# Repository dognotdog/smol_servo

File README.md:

# Project Layout

## firmware48

Contains files specific to 48pin STM32G431 on the stm32-nema17-servo board.

## mechaduino-firmware

Firmware for Mechaduino's SAMD21G18A Cortex M0+.

## hardware

Hardware design files for Schematic and PCB.

## tests

There is a basic harness in place to use [Unity](https://github.com/ThrowTheSwitch/Unity) for unit testing. Create `foo_test.c` modules for testing, and `foo_test.mk` makefiles for additional setup.

# Calculations

### Current Sense Shunt Resistor Value

Rated continous current 8A, max. Bus Voltage 50V, min. load 1R

 - 1206 can dissipate 1.5W usually, using a conservative 1W for the rated current: P/I^2 -> Rs < 15.6mOhm

With a 1R load on a 50V bus, up to 50A could flow at once, but hopefully motor inductance smoothes that out. Assuming 50kHz, 2mH winding inductance:
	V = L * di/dt -> di/dt = V/L = 25kA/s @ 50kHz = 0.5 A/cycle

### Gate Drive

The required charge pump current is
	I_VCP = 3 * Q_G * f_PWM.

DRV8323 charge pump VBUS limits:
6V -> 10mA
8V -> 15mA
10V -> 20mA
13V -> 25mA

#### NTTFS4937N

Q_G = 35.5 nC

I_VCP = 3.55 mA @ 100kHz
I_VCP = 1.78 mA @ 50kHz

Charge pump current capacity is well over required charge pump current.

#### FDMC86570L

Q_G < 88 nC

I_VCP = 8.8 mA @ 100kHz
I_VCP = 4.4 mA @ 50kHz

#### FDMC86183

Q_G ~ 15 nC
Q_gd ~ 3.4 nC

### Passive NSS OR circuit

3.3V, 5pF gate capacitance, 8mA sink/source per pin -> 412.5 Ohm minimum resistance

f_RC = 1 / 2pi R C

for R=470 that is 67.7MHz
for R=1k that is 31.8MHz
for R=2.2k that is 14.4MHz

max SPI frequency is 10MHz. 1k for both lines seems sufficiently fast and will not exceed max current on pin. Only one will be actively pulled high, the other will be in high impedance mode, but 1k is safe even if both are actively driven against the NSS pin.

# Electrical Motor Driving

## RL Circuit
The principal equation for an RL circuit, as is assumed for a motor winding, describing the relationship between voltage and current is:
`V = L * di/dt + R i`
or in differential form
```
	        V - R i
	di/dt = -------
	           L
```

### Discrete Time RL Equation

In discrete time, with n=0,1,2... indices going backward in time, the equation becomes
`V_0 = L * (i_0 - i_1) / T + R i_0`
solving for L
```
      V_0 - R i_0
L = T -----------
       i_0 - i_1
```
solving for R
```
    V_0 - L * (i_0 - i_1) / T
R = -------------------------
               i_0
```
assuming a measurement at n=0 for R and n=1 for L, and substituting
```
                V_0 - L * (i_0 - i_1) / T
      V_1 - i_1 -------------------------
                           i_0
L = T -----------------------------------
                 i_1 - i_2

      V_1 i_0 - i_1 V_0     i_1 (i_0 - i_1)
L = T ----------------- + L ---------------
       i_0 (i_1 - i_2)      i_0 (i_1 - i_2)        

               V_1 i_0 - i_1 V_0 
L = T ----------------------------------
       i_0 (i_1 - i_2) - i_1 (i_0 - i_1)        

      V_1 i_0 - i_1 V_0          i_0 - i_1
L = T ----------------- = T V ---------------
       i_1^2 - i_0 i_2        i_1^2 - i_0 i_2

          V_1 - R i_1
    V_0 - ----------- (i_0 - i_1)
           i_1 - i_2
R = -----------------------------
                i_0

    V_0 (i_1 - i_2) - V_1 (i_0 - i_1) + R i_1 (i_0 - i_1)
R = -----------------------------------------------------
                      i_0 (i_1 - i_2)

    V_0 (i_1 - i_2) - V_1 (i_0 - i_1)
R = ---------------------------------
    i_0 (i_1 - i_2) - i_1 (i_0 - i_1)

    V_0 (i_1 - i_2) - V_1 (i_0 - i_1)     2 i_1 - i_2 - i_0
R = --------------------------------- = V -----------------
             i_1^2 - i_0 i_2               i_1^2 - i_0 i_2

       L         i_0 - i_1
tau = --- = T -----------------
       R      2 i_1 - i_2 - i_0
```

# Stepper Control

A Bipolar hybrid stepper motor typically has 200 steps/rev on 2 phases.

An electrical revolution is four full steps: 
A+ -> B+ -> A- -> B-

NEMA 17 typically up to 3A current (eg. Nanotec ST4118D3004)""

winding current: 3A
winding inductance: 2.7mH 
winding resistance: 1.1R
Holding Torque: 0.8Nm
Rotor Inertia: 1.02e-5 Kg m^2
Torque Constant (mech): 0.267 Nm / A [or V / rad s]

At 48V, the motor should be able to spin (theoretically, discounting nonlinear effects) at 179.7 rad/s, about 1716 rpm or 28.6 rev/s.

at 30 rev/s with 200 steps/rev, we have to make 6000 full steps per second.

# BLDC Control

A BLDC has 3 phases, which are most simplistically driven with trapezoidal voltage curves instead of sinusoidal ones.
```
      _       _
A   /   \   /
  -       -
        _      
B \   /   \   /
    -       -
  _       _      
C   \   /   \   
      -       -
```

A ~ sin(alpha)
B ~ sin(alpha + 2pi/3)
C ~ sin(alpha + 4pi/3)

In a typical configuration, the three windings A,B,C are connected in a star pattern, with the endpoints named U,V,W.
```
V       U
B \   / A	    
    *       
    | C
    W
```
A = 

U-V 	= A
V-W 	= B-C = sin(a + 2pi/3) - sin(a + 4pi/3) 
	= sin(a) cos(2pi/3) + cos(a) sin(2pi/3) - sin(a) cos (4pi/3) - cos(a) sin(4pi/3)
	= sin(a) - sqrt(3) cos(a)
W-U = C-A

# STM32G431 Setup

## USB

Crystal-less USB Setup in MX
 - USB clock source should be `HSI48`1
 - set `CRS SYNC` to `USB_FS` in RCC Mode & Config
 - enable `Sof Enable` in USB device settings

Full-Speed USB (12Mbps) has a max. packet size of 64 bytes for regular packets, only isochronous might be up to 1023.

### CDC
 - increase `APP_RX_DATA_SIZE` and `APP_TX_DATA_SIZE` to at least 64
 - add at least 7 byte persistent buffer to store data from `CDC_SET_LINE_CODING` that can be output on `CDC_GET_LINE_CODING`

## Peripheral usage

ADC1: internal sensors, voltage reference
ADC2: CH3, CH13, CH17 inputs for current sense resistors, from V0.2 CH14 for VBUS sense

I2C3: I2C for communicating with the outside world
SPI2: connected to MOSFET driver and encoder ICs
USART1: external UART

TIM2: CH1 brake resistor, CH2,CH3,CH4 A,B,C PWM outputs for half bridges
TIM3: external quadrature encoder input
TIM4: CH1,CH2,CH3 LED RGB PWM output (CH4 connects to SYNC)
TIM6: Timer for performance counter with PSC=169 to get a 1us count resolution @ 170MHz clock

TIM1,TIM7,TIM8,TIM15,TIM16,TIM17: unused

# Blackmagic Probe debugging

Firmware update for probe:
`dfu-util -d 1d50:6018,:6017 -s 0x08002000:leave -D <blackmagic-native.bin>`

## GDB

```
~/Applications/ARM-Toolchain/gcc-arm-none-eabi-8-2019-q3-update/bin/arm-none-eabi-gdb
target extended-remote /dev/cu.usbmodem79A760B81
monitor swdp_scan
attach 1
```

# Board Revisions

## V0.6.0 (TMC6200)
 - C22 (0.022uF 100V) is not available in 0402, thus 2 10n caps in parallel have to be used, stacked on top of each other.

## V0.4

### Changes
 - Change to 4-layer board for better power planes, and to de-clutter some of the signal paths.
 - Change USB-C socket footprint to be compatible two variants

## V0.3.1

### Known Bugs
 - (16.b) no zeners on VBUS/VDDP monitor taps means no chip protection

### Bugfixes
 - (15) move motor connector out by another 25mil
 - (16.a) 100n cap instead of zeners on VBUS/VDDP give much better accuracy
 - (17) add ground traces for current sense amps

### Observations
 - (17) it looks as though A and C bridges are measuring current much closer together with the dedicated ground traces

## V0.3

### Known Bugs
 - (15) motor connector does not have enough clearance for connection from back
 - (16) adding small buffer caps (100n) on voltage dividers for VBUS/VDDP would help with inaccuracy due to high-impedance source.
 - (17) current sense traces are not routed differentially, need ground lines directly to sense resistors instead of via ground plane to prevent induced effects

### Bugfixes
 - (3) change footprint of L2 from 0806 to 1005
 - (10) connects DRV8323 VREF to 3V3 plane
 - (11) connects STM32G4 VREF to 3V3 plane
 - (12) correct B1/B12 spacing on USB-C receptacle footprint
 - (13) Change D3 to ABRG and switch B/G channels on STM32G4
 - (14) move VDDDIV to PF0-ADC1_IN10
 - (8) with VDDDIV moved, re-connected hardware NSS, as STM32G4 should be able to pulse it between frames for proper DMA transfers with NSSP enabled, and add passive OR-ing resistors so that chip can be selected.

### Enhancements
 - Add 500mA polyfuse to USB 5V input to protect the input diode (and host) in case of VDD short to ground
 - change D2 to bigger footprint to be able to fit bigger diode with appropriate voltage rating

### Software Differences

Correction: Hardware NSS does NOT work because it requires opposite clock signal polarity :/

Enable hardware NSS control as master with pulsing between data words

- hspi2.Init.NSS = SPI_NSS_SOFT;
+ hspi2.Init.NSS = SPI_NSS_HARD_OUTPUT;

- hspi2.Init.NSSPMode = SPI_NSS_PULSE_DISABLE
+ hspi2.Init.NSSPMode = SPI_NSS_PULSE_ENABLE

This enables use of DMA transfers for reading data from sensors.

## V0.2

### Known Bugs
 - (10) VREF pin of DRV8323 not connected to 3V3
 - (11) VREF pin of STM32G4 not connected to 3V3
 - (12) USB-C receptacle footprint slightly wrong, spacing of B1/B12 pins too narrow for easy fit
 - (13) Wrong Pinout for D3, was RGBA should be ABRG
 - (14) sensing VDD connected to PA15 doesn't work as PA15 can only be a trigger input, not an analog channel, PF0 is the only available pin with an analog channel on ADC1

### Bugfixes
 - (1): adds bus voltage analog input to PB11, moves DRVSEL to PB12 (nixing NSS, see (8))
 - (2): connect B4/B9 pins on USB connectors
 - (5): Q8/9/10 changed be GSD in schematic, as they should be for the SSM3K35CTC, resulting in 180deg rotation
 - (6): moved C3 a nudge further away from DM via
 - (7): force thermals on J4 and J5
 - (8) Remove U2 and DRVSCS/ASCS lines and replace them directly with DRVSEL/ASEL
 - (9) Add R30 as 10K pullup on MISO

### Enhancements

#### Additional VBUS Cap

Adds two additional 10uF capacitor to VBUS, for a total of 60uF capacitance. For a 50V bus, and a 1R load, which is 50A max current, and 50kHz PWM, that means a single full PWM cycle can drain `50*20e-6 = 1000 uC`. At 50v, the cap charge is 3000uC, so the bus voltage could still drop by nearly 20V without an external buffer cap.

Same load with 10V, it's a 10A max and thus only a 100uC discharge, which is a 2V drop, or again 20% of bus voltage.

VBUS caps have been relocated so that each FET pair gets one next to it, plus one at the VBUS input.

#### VDD and VBUS sense dividers

Sensing VBUS was added for controlling the brake resistor when the voltage rises too much.

Sensing VDD is for ...?

#### Portruding power connectors

Power connectors have been moved to portrude from the 42x42mm footprint, so that the board can be mounted on the back surface or very close to the back surface of a motor without the through-hole power connectors being in danger of touching the motor casing.

## V0.1

### Known Bugs
 - (1) No feedback of bus voltage to measure it, to be able to drive brake resistor accordingly
 - (2) USB B4 and B9 not connected
 - (3) L2 probbaly has too small a footprint (BRL3225T2R2M is too large, though seems to solder ok)
 - (4) stencil cutouts too small for the high density IC pins (vreg especially), not enough solder is on pins to make good contact on reflow
 - (5) LED driver transistors Q8/9/10 are pinned wrong, should be GSD for SSM3K35CTC
 - (6) C3's 3V3 pad too close to DM via, though boards seemed to have come out fine
 - (7) VBUS pad on J4 and OR pad on J5 connector have no thermals for hand-soldering
 - (8) SPI hardware is incapable of doing word-wise NSS triggering, thus the whole logic dance with U2 may not be necessary, as we can just do software SS from GPIO
 - (9) 10K pullup might be required for DRV8323 on MISO line
 - (10) VREF pin of DRV8323 not connected to 3V3
 - (11) VREF pin of STM32G4 not connected to 3V3
 - (12) USB-C receptacle footprint slightly wrong, spacing of B1/B12 pins too narrow for easy fit
 - (13) Wrong Pinout for D3, was RGBA should be ABRG

### Status

 - USB CDC output works
 - SPI to both AD5047D and DRV8323 work after fixing bug (9)
 - all power transistors are switched under a no load condition, with DRV8323 in 3xPWM mode

# Alternate Parts

## STM32G431CxU
G441, G491, GG4A1, G473, G483, G474, G484

### NRF5340

The nRF5340 is the successor of the nRF52 series, and is a dual-core design at 128MHz and 64MHz, respectively

#### ADC

The ADC can be configured for acquisition times between 3 and 40 us, with a minimum of 10us for VDD monitoring. The conversion time is 2us, giving us a max. sample rate of 200kHz

#### Timers / PWM

The timers only run at 16MHz, which at 100kHz would only give a resolution of 160 counts for a PWM signal. This is compared to the full 168MHz resolution of the STM32G4, giving 1680 counts, roughly 10x the resolution, for an effective 10 bits vs 7 bits.

### LPC5528JEV98K

An ARM Cortex M33 core @ 150MHz, in a 0.5mm pitch BGA package.

### ADuCM410

2 MSPS 16bit ADC, 160 MHz ARM Cortex M33, 5x5mm, 0.5mm pitch BGA

### ATSAM4S

120MHz ARM Cortex M4, no FPU though. 100pin BGA 7x7, 0.65mm pitch.

## DRV8323RS

This part has both the 3ph driver and current sense.

### DRV8353R

Higher voltage, similar part

### DRV8300NRGR + INAxxx

The DRV8300 needs extra current sense amplifiers and a high-side bootstrap, pluss VDD supply. Looks like INA190 or INA210 can do bidirectional sensing

### TMC6200

### FDMF2011

interesting integrated half bridge for up to 20A

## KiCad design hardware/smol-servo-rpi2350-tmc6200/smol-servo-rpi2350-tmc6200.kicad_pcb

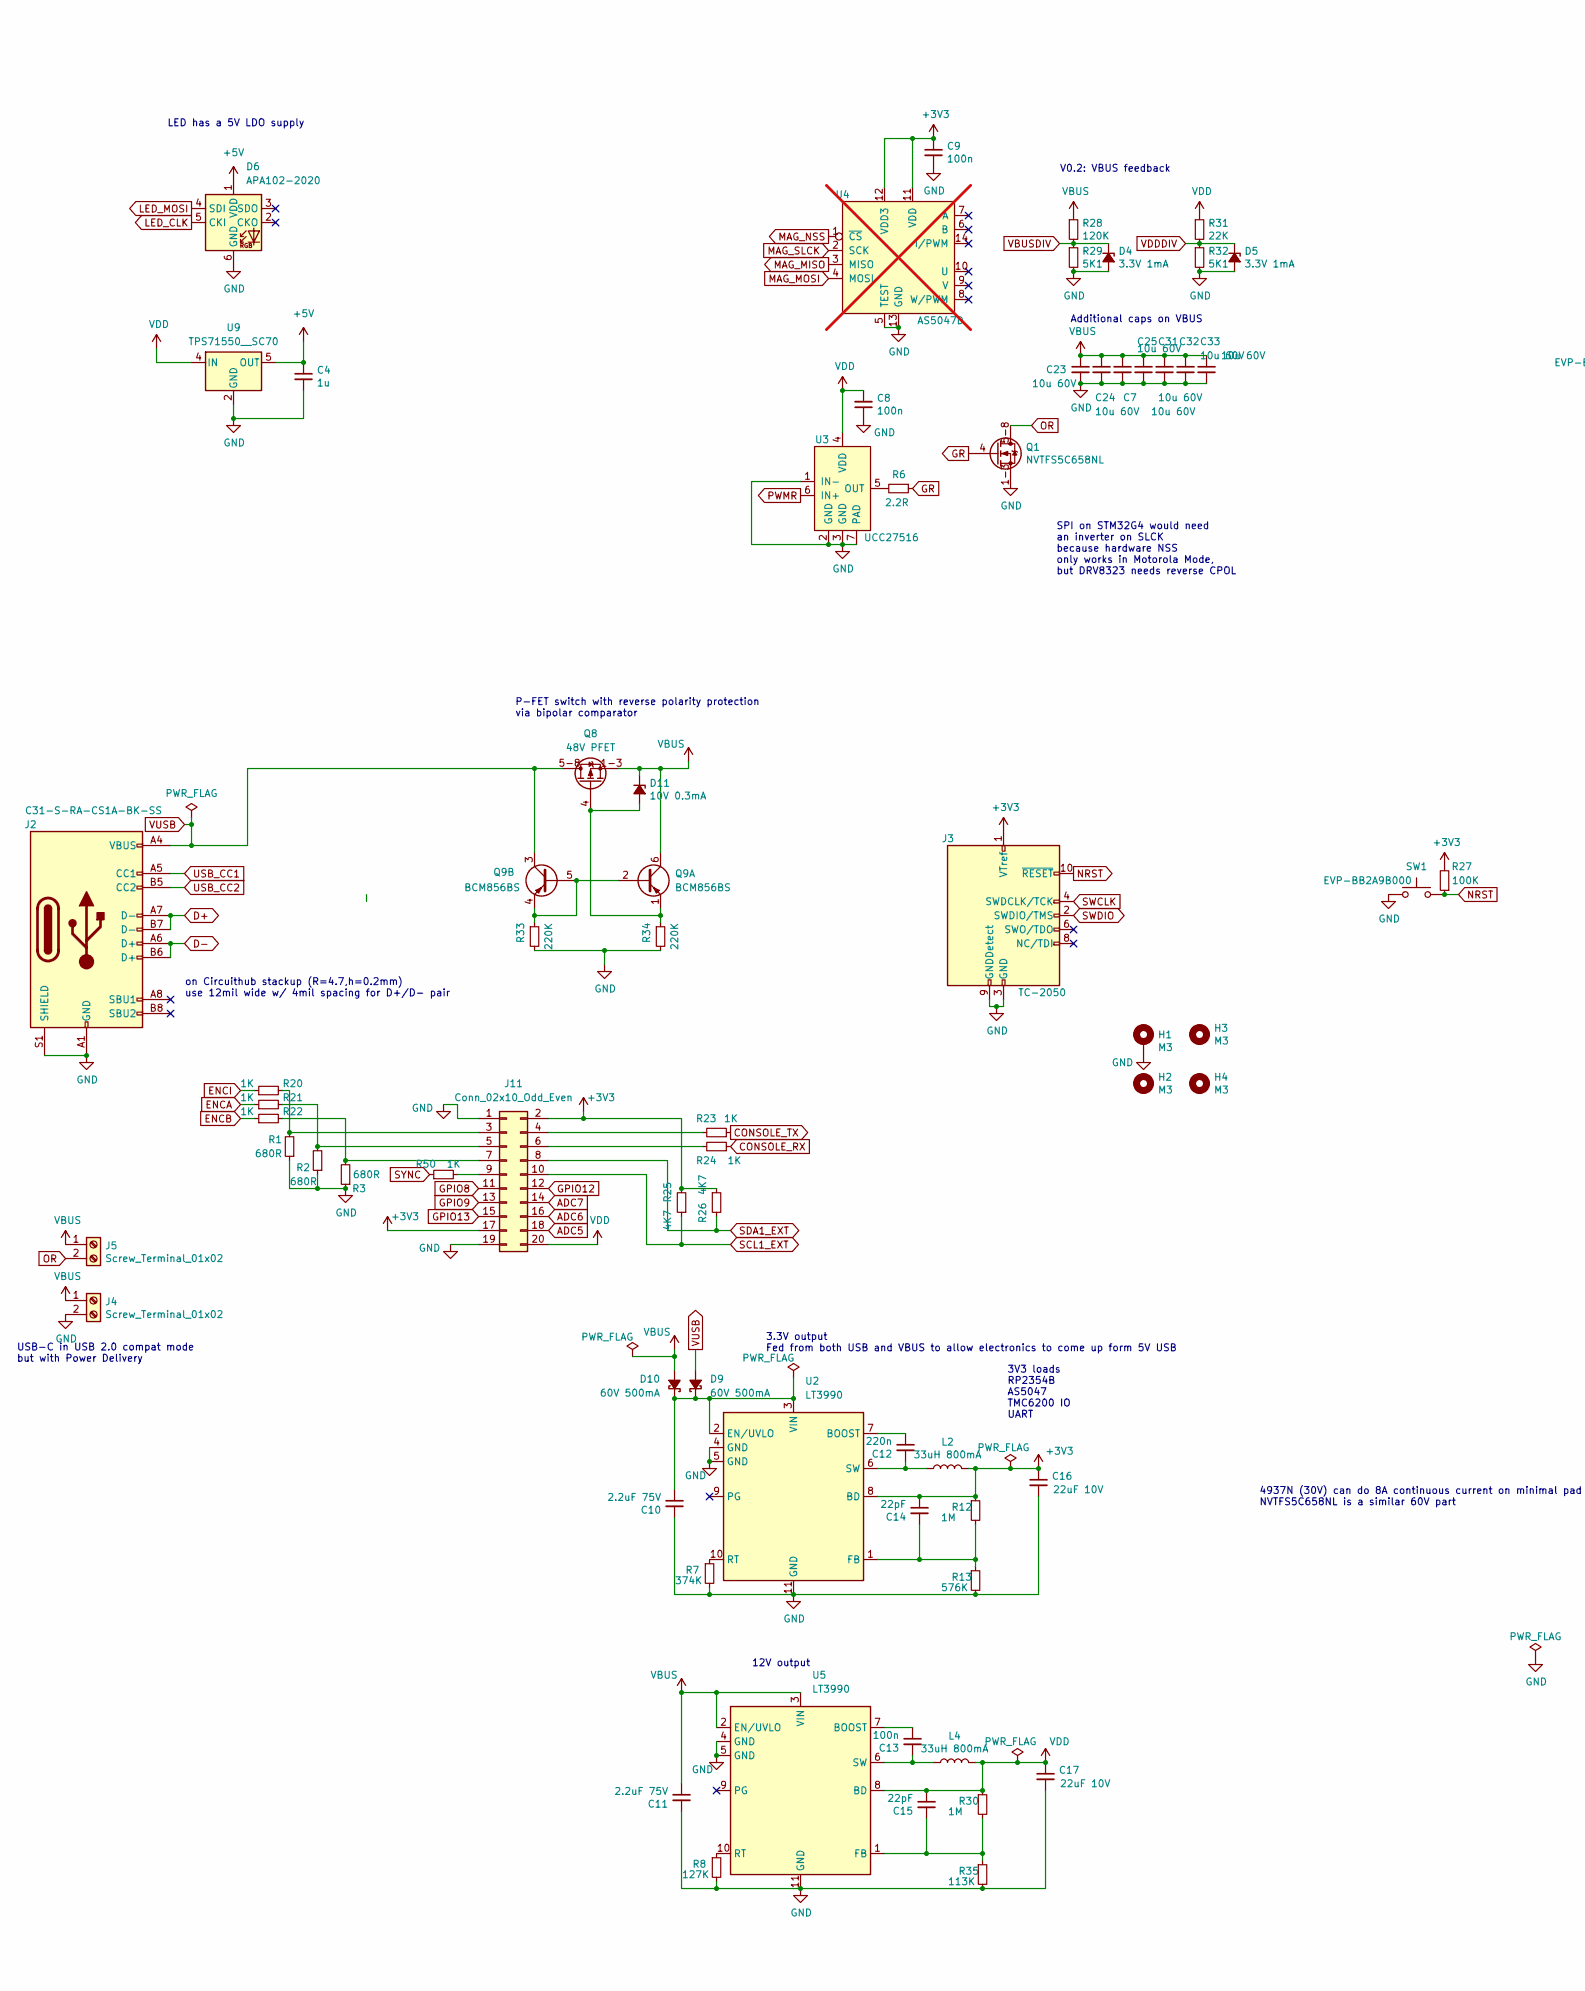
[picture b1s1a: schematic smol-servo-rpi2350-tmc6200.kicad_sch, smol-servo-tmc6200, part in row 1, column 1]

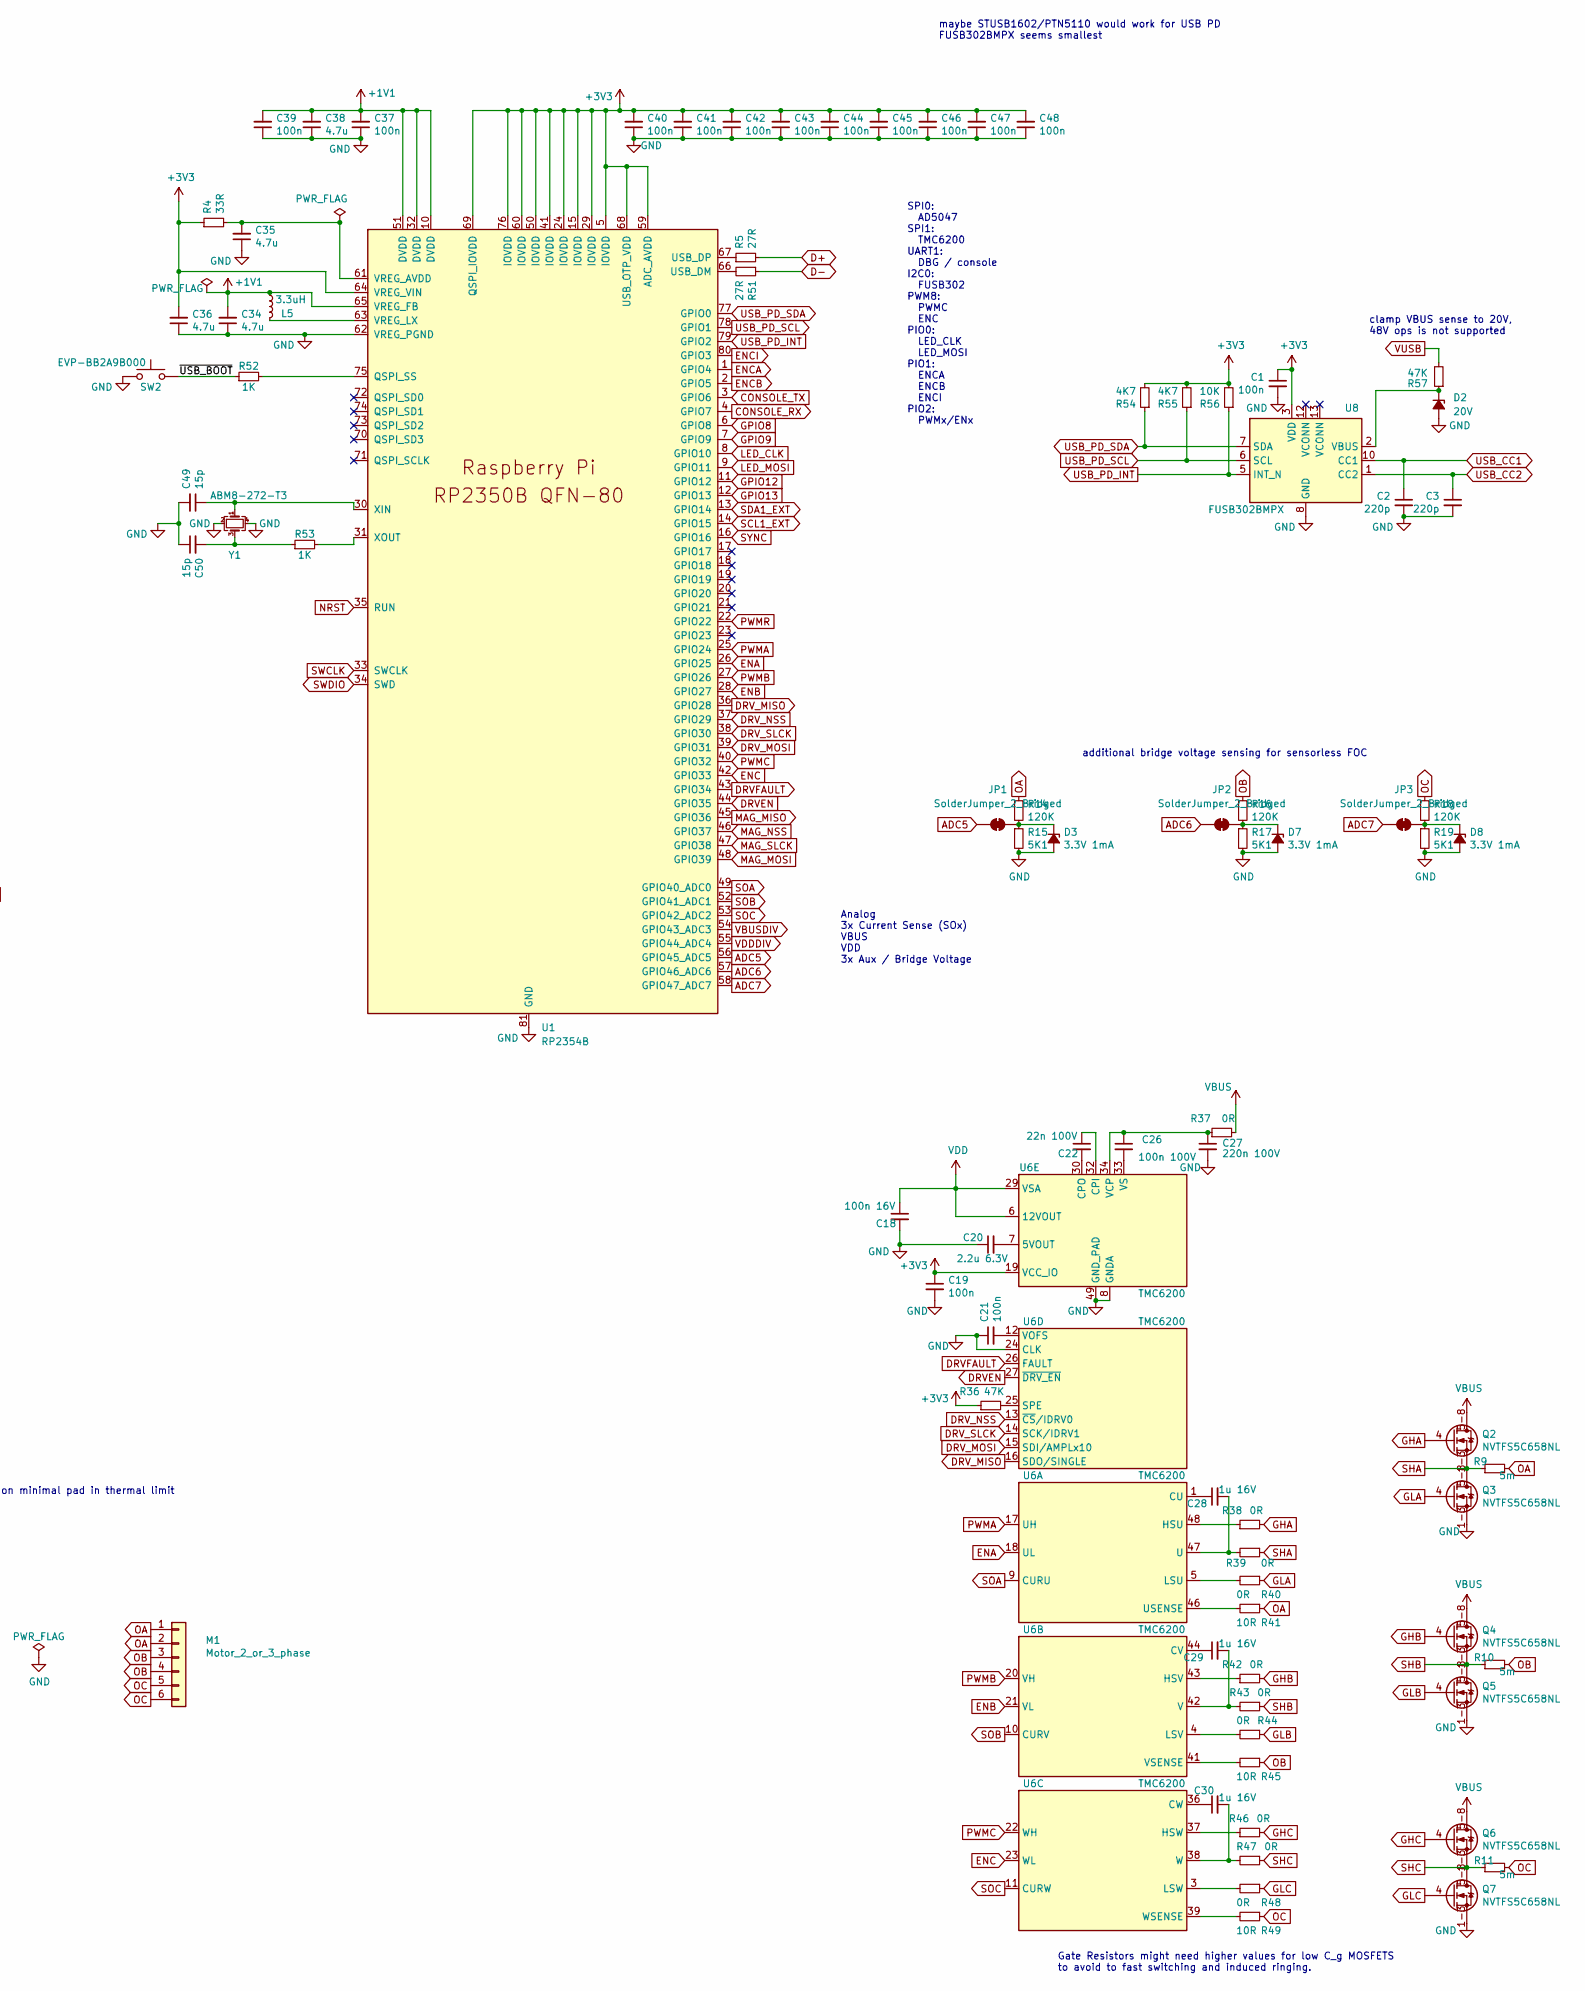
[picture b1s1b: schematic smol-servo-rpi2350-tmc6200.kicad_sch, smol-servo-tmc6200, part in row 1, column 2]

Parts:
C1, C8, C9, C13, C19, C21, C37, C39, C40, C41, C42, C43, C44, C45, C46, C47, C48: 100n; C_0402_1005Metric; MPN CC0402KRX5R8BB104; JLCPCB C5137468
C2, C3: 220p; C_0402_1005Metric; MPN CC0402KRX5R8BB224; JLCPCB C39122
C4: 1u; C_0402_1005Metric; MPN CC0402KRX5R8BB105; JLCPCB C14445
C7, C23, C24, C25, C31, C32, C33: 10u 60V; C_1210_3225Metric; MPN C3225X7R1N106K250AC;CGA6P1X7R1N106M250AC; JLCPCB C5156756
C10, C11: 2.2uF 75V; C_0805_2012Metric; MPN GRM21BD72A225ME01K; JLCPCB C2981733
C12: 220n; C_0402_1005Metric; MPN CL05B224KO5NNNC; JLCPCB C16772
C14, C15: 22pF; C_0402_1005Metric; MPN CL05C220JB5NNNC; JLCPCB C1555
C16, C17: 22uF 10V; C_0603_1608Metric; MPN CM105X5R226M16AT;CL10A226MP8NUNE; JLCPCB C84419
C18: 100n 16V; C_0402_1005Metric; MPN CC0402KRX5R8BB104; JLCPCB C5137468
C20: 2.2u 6.3V; C_0402_1005Metric; MPN GRM155C80J225KE95D; JLCPCB C12530
C22: 22n 100V; C_0603_1608Metric; MPN C1608X7R2A223K080AA; JLCPCB C376821
C26: 100n 100V; C_0402_1005Metric; MPN GRM155R62A104ME14D; JLCPCB C162178
C27: 220n 100V; C_0603_1608Metric; MPN HMK107C7224KAHTE; JLCPCB C36911431
C28, C29, C30: 1u 16V; C_0402_1005Metric; MPN CL05A105KO5NNNC; JLCPCB C29266
C34, C35, C36, C38: 4.7u; C_0402_1005Metric; MPN CC0402MRX5R6BB475; JLCPCB C23733
C49, C50: 15p; C_0402_1005Metric; MPN CC0402JRNPO8BN150; JLCPCB C106997
D2: 20V; D_0603_1608Metric; MPN CZRU52C20;BZX584B20V; JLCPCB C968162
D3, D4, D5, D7, D8: 3.3V 1mA; D_0402_1005Metric; MPN CZRQR3V3B-HF; JLCPCB C3013401
D6: APA102-2020; LED-APA102-2020; MPN BB-2020BGR-TRB; JLCPCB C22439302
D9, D10: 60V 500mA; D_SOD-882; MPN PMEG6010ESBYL; JLCPCB C552935
D11: 10V 0.3mA; D_0402_1005Metric; MPN CZRQR10VB-HF;PZU10B2L,315; JLCPCB C553572
H1: M3; MountingHole_3.2mm_M3_DIN965_Pad
H2, H3, H4: M3; MountingHole_3.2mm_M3
J2: C31-S-RA-CS1A-BK-SS; USB_C_Receptacle_Adam_C31-S-RA-CS1X-BK; MPN C31-S-RA-CS1A-BK-SS;C31-S-RA-CS1E-BK-SS; JLCPCB C6582279
J3: TC-2050; Tag-Connect_TC2050-IDC-NL_2x05_P1.27mm_Vertical
J4, J5: Screw_Terminal_01x02; TerminalBlock_Phoenix_PT-1,5-2-3.5-H_1x02_P3.50mm_Horizontal
J11: Conn_02x10_Odd_Even; PinHeader_2x10_P1.00mm_Vertical
JP1, JP2, JP3: SolderJumper_2_Bridged; SolderJumper-2_P1.3mm_Bridged_RoundedPad1.0x1.5mm
L2, L4: 33uH 800mA; L_Taiyo-Yuden_NR-40xx; MPN TYS4030330M;MDWK4040T330MM; JLCPCB C2849475
L5: 3.3uH; L_pol_2016; MPN AOTA-B201610S3R3-101-T; JLCPCB C42411119
M1: Motor_2_or_3_phase; PinHeader_1x06_P2.54mm_Vertical
Q1, Q2, Q3, Q4, Q5, Q6, Q7: NVTFS5C658NL; WDFN8; MPN NVTFS5C658NL;NTTFS012N10MDTAG; JLCPCB C5208924
Q8: 48V PFET; WDFN8
Q9: BCM856BS; SOT-363_SC-70-6
R1, R2, R3: 680R; R_0402_1005Metric; MPN RC0402JR-07680RL; JLCPCB C25130
R4: 33R; R_0402_1005Metric; MPN RC0402FR-0733RL; JLCPCB C25105
R5, R51: 27R; R_0402_1005Metric; MPN RC0402FR-0727RL; JLCPCB C25100
R6: 2.2R; R_0402_1005Metric; MPN RC0402FR-072R2L; JLCPCB C25101
R7: 374K; R_0402_1005Metric; MPN RC0402FR-07374KL; JLCPCB C25781
R8: 127K; R_0402_1005Metric; MPN RC0402FR-07127KL; JLCPCB C11688
R9, R10, R11: 5m; R_1206_3216Metric; MPN PA1206FRF7W0R005L; JLCPCB C875584
R12, R30: 1M; R_0402_1005Metric; MPN RC0402FR-071ML; JLCPCB C26083
R13: 576K; R_0402_1005Metric; MPN RC0402FR-07576KL; JLCPCB C27012
R14, R16, R18, R28: 120K; R_0402_1005Metric; MPN RC0402FR-07120KL; JLCPCB C25750
R15, R17, R19, R29, R32: 5K1; R_0402_1005Metric; MPN RC0402FR-075K1L; JLCPCB C25905
R20, R21, R22, R23, R24, R50, R52, R53: 1K; R_0402_1005Metric; MPN RC0402FR-071KL; JLCPCB C11702
R25, R26, R54, R55: 4K7; R_0402_1005Metric; MPN RC0402FR-074K7L; JLCPCB C25900
R27: 100K; R_0402_1005Metric; MPN RC0402FR-07100KL; JLCPCB C25741
R31: 22K; R_0402_1005Metric; MPN RC0402FR-0722KL; JLCPCB C25768
R33, R34: 220K; R_0402_1005Metric; MPN RC0402FR-072R2L; JLCPCB C25767
R35: 113K; R_0402_1005Metric; MPN RC0402FR-07113KL; JLCPCB C25746
R36, R57: 47K; R_0402_1005Metric; MPN RC0402FR-0747KL; JLCPCB C25792
R37, R38, R39, R40, R42, R43, R44, R46, R47, R48: 0R; R_0402_1005Metric; MPN RC0402FR-070RL; JLCPCB C17168
R41, R45, R49: 10R; R_0402_1005Metric; MPN RC0402FR-0710RL; JLCPCB C102766
R56: 10K; R_0402_1005Metric; MPN RC0402FR-0710KL; JLCPCB C25744
SW1, SW2: EVP-BB2A9B000; SW_SPST_EVPBB; MPN EVP-BB2A9B000; JLCPCB C4365176
U1: RP2354B; RP2350-QFN-80-1EP_10x10_P0.4mm_EP3.4x3.4mm_ThermalVias; MPN RP2354B; JLCPCB C39843328
U2, U5: LT3990; DFN-10-1EP_3x3mm_P0.5mm_EP1.65x2.38mm_ThermalVias; MPN LT3990*DD; JLCPCB C580169
U3: UCC27516; Texas_PWSON-N6; MPN UCC27516; JLCPCB C3655221
U4: AS5047D; TSSOP-14_4.4x5mm_P0.65mm-inlaid; MPN AS5047D; not fitted
U6: TMC6200; TQFP-48-1EP_7x7mm_P0.5mm_EP5x5mm_ThermalVias; MPN TMC6200; JLCPCB C465958
U8: FUSB302BMPX; WQFN-14-1EP_2.5x2.5mm_P0.5mm_EP1.45x1.45mm; MPN FUSB302BMPX; JLCPCB C132291
U9: TPS71550__SC70; SOT-353_SC-70-5; MPN TPS71550; JLCPCB C571193
Y1: ABM8-272-T3; Oscillator_SMD_Abracon_ASE-4Pin_3.2x2.5mm; MPN ABM8-272-T3; JLCPCB C20625731

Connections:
+1V1: C34.2, C37.2, C38.2, C39.2, L5.1, U1.10 (DVDD), U1.32 (DVDD), U1.51 (DVDD), U1.65 (VREG_FB)
+3V3: C1.1, C9.1, C14.1, C16.1, C19.1, C36.2, C40.2, C41.2, C42.2, C43.2, C44.2, C45.2, C46.2, C47.2, C48.2, J3.1 (VTref), J11.2, J11.17, L2.2, R4.1, R12.1, R25.2, R26.1, R27.2, R36.1, R54.2, R55.2, R56.2, U1.5 (IOVDD), U1.15 (IOVDD), U1.24 (IOVDD), U1.29 (IOVDD), U1.41 (IOVDD), U1.50 (IOVDD), U1.59 (ADC_AVDD), U1.60 (IOVDD), U1.64 (VREG_VIN), U1.68 (USB_OTP_VDD), U1.69 (QSPI_IOVDD), U1.76 (IOVDD), U2.8 (BD), U4.11 (VDD), U4.12 (VDD3), U6.19 (VCC_IO), U8.3 (VDD), U8.4 (VDD)
+5V: C4.1, D6.1 (VDD), U9.5 (OUT)
/~USB_BOOT: R52.1, SW2.2
ADC5: J11.18, JP1.1 (A), U1.56 (GPIO45_ADC5)
ADC6: J11.16, JP2.1 (A), U1.57 (GPIO46_ADC6)
ADC7: J11.14, JP3.1 (A), U1.58 (GPIO47_ADC7)
CONSOLE_RX: R24.1, U1.4 (GPIO7)
CONSOLE_TX: R23.1, U1.3 (GPIO6)
D+: J2.A7 (D-), J2.B7 (D-), R5.2
D-: J2.A6 (D+), J2.B6 (D+), R51.1
DRVEN: U1.44 (GPIO35), U6.27 (~DRV_EN)
DRVFAULT: U1.43 (GPIO34), U6.26 (FAULT)
DRV_MISO: U1.36 (GPIO28), U6.16 (SDO/SINGLE)
DRV_MOSI: U1.39 (GPIO31), U6.15 (SDI/AMPLx10)
DRV_NSS: U1.37 (GPIO29), U6.13 (~CS/IDRV0)
DRV_SLCK: U1.38 (GPIO30), U6.14 (SCK/IDRV1)
ENA: U1.26 (GPIO25), U6.18 (UL)
ENB: U1.28 (GPIO27), U6.21 (VL)
ENC: U1.42 (GPIO33), U6.23 (WL)
ENCA: R21.1, U1.1 (GPIO4)
ENCB: R22.1, U1.2 (GPIO5)
ENCI: R20.1, U1.80 (GPIO3)
GHA: Q2.4 (G), R38.2
GHB: Q4.4 (G), R42.2
GHC: Q6.4 (G), R46.2
GLA: Q3.4 (G), R40.1
GLB: Q5.4 (G), R44.1
GLC: Q7.4 (G), R48.1
GND: C1.2, C2.2, C3.2, C4.2, C7.2, C8.1, C9.2, C10.2, C11.2, C16.2, C17.2, C18.2, C19.2, C20.1, C21.1, C23.2, C24.2, C25.2, C27.2, C31.2, C32.2, C33.2, C34.1, C35.1, C36.1, C37.1, C38.1, C39.1, C40.1, C41.1, C42.1, C43.1, C44.1, C45.1, C46.1, C47.1, C48.1, C49.2, C50.1, D2.2 (A), D3.2 (A), D4.2 (A), D5.2 (A), D6.6 (GND), D7.2 (A), D8.2 (A), H1.1, J2.A1 (GND), J2.A12 (GND), J2.B1 (GND), J2.B12 (GND), J2.S1 (SHIELD), J3.3 (GND), J3.5 (GND), J3.9 (GNDDetect), J4.2, J11.1, J11.19, Q1.1-3 (S), Q3.1-3 (S), Q5.1-3 (S), Q7.1-3 (S), R1.1, R2.1, R3.1, R7.2, R8.2, R13.2, R15.2, R17.2, R19.2, R29.2, R32.2, R33.2, R34.2, R35.2, SW1.1, SW2.1, U1.62 (VREG_PGND), U1.81 (GND), U2.4 (GND), U2.5 (GND), U2.11 (GND), U3.1 (IN-), U3.2 (GND), U3.3 (GND), U3.7 (PAD), U4.5 (TEST), U4.13 (GND), U5.4 (GND), U5.5 (GND), U5.11 (GND), U6.8 (GNDA), U6.24 (CLK), U6.49 (GND_PAD), U8.8 (GND), U8.9 (GND), U8.15 (GND), U9.2 (GND), Y1.2, Y1.4
GPIO8: J11.11, U1.6 (GPIO8)
GPIO9: J11.13, U1.7 (GPIO9)
GPIO12: J11.12, U1.11 (GPIO12)
GPIO13: J11.15, U1.12 (GPIO13)
GR: Q1.4 (G), R6.1
LED_CLK: D6.5 (CKI), U1.8 (GPIO10)
LED_MOSI: D6.4 (SDI), U1.9 (GPIO11)
MAG_MISO: U1.45 (GPIO36), U4.3 (MISO)
MAG_MOSI: U1.48 (GPIO39), U4.4 (MOSI)
MAG_NSS: U1.46 (GPIO37), U4.1 (~CS)
MAG_SLCK: U1.47 (GPIO38), U4.2 (SCK)
NRST: J3.10 (~RESET), R27.1, SW1.2, U1.35 (RUN)
unnamed: C50.2, R53.1, Y1.3
unnamed: D2.1 (K), R57.1, U8.2 (VBUS)
unnamed: D3.1 (K), JP1.2 (B), R14.2, R15.1
unnamed: D7.1 (K), JP2.2 (B), R16.2, R17.1
unnamed: D8.1 (K), JP3.2 (B), R18.2, R19.1
unnamed: C10.1, D9.1 (K), D10.1 (K), U2.2 (EN/UVLO), U2.3 (VIN)
unnamed: D11.2 (A), Q8.4 (G), Q9.1 (E1), R34.1
unnamed: J11.3, R1.2, R20.2
unnamed: J11.4, R23.2
unnamed: J11.5, R2.2, R21.2
unnamed: J11.6, R24.2
unnamed: J11.7, R3.2, R22.2
unnamed: J11.9, R50.2
unnamed: Q9.2 (B1), Q9.4 (E2), Q9.5 (B2), R33.1
unnamed: R52.2, U1.75 (QSPI_SS)
unnamed: R51.2, U1.66 (USB_DM)
unnamed: R5.1, U1.67 (USB_DP)
unnamed: C35.2, R4.2, U1.61 (VREG_AVDD)
unnamed: L5.2, U1.63 (VREG_LX)
unnamed: C49.1, U1.30 (XIN), Y1.1
unnamed: R53.2, U1.31 (XOUT)
unnamed: C12.1, U2.7 (BOOST)
unnamed: C14.2, R12.2, R13.1, U2.1 (FB)
unnamed: R7.1, U2.10 (RT)
unnamed: C12.2, L2.1, U2.6 (SW)
unnamed: R6.2, U3.5 (OUT)
unnamed: C13.1, U5.7 (BOOST)
unnamed: C15.2, R30.2, R35.1, U5.1 (FB)
unnamed: R8.1, U5.10 (RT)
unnamed: C13.2, L4.1, U5.6 (SW)
unnamed: C28.1, U6.1 (CU)
unnamed: R38.1, U6.48 (HSU)
unnamed: R40.2, U6.5 (LSU)
unnamed: C28.2, R39.2, U6.47 (U)
unnamed: R41.2, U6.46 (USENSE)
unnamed: C29.1, U6.44 (CV)
unnamed: R42.1, U6.43 (HSV)
unnamed: R44.2, U6.4 (LSV)
unnamed: C29.2, R43.2, U6.42 (V)
unnamed: R45.2, U6.41 (VSENSE)
unnamed: C30.1, U6.36 (CW)
unnamed: R46.1, U6.37 (HSW)
unnamed: R48.2, U6.3 (LSW)
unnamed: C30.2, R47.2, U6.38 (W)
unnamed: R49.2, U6.39 (WSENSE)
unnamed: R36.2, U6.25 (SPE)
unnamed: C21.2, U6.12 (VOFS)
unnamed: C20.2, U6.7 (5VOUT)
unnamed: C22.1, U6.32 (CPI)
unnamed: C22.2, U6.30 (CPO)
unnamed: C26.1, C27.1, R37.1, U6.34 (VCP)
unnamed: C26.2, U6.33 (VS)
OA: M1.1, M1.2, R9.2, R14.1, R41.1
OB: M1.3, M1.4, R10.2, R16.1, R45.1
OC: M1.5, M1.6, R11.2, R18.1, R49.1
OR: J5.2, Q1.5-8 (D)
PWMA: U1.25 (GPIO24), U6.17 (UH)
PWMB: U1.27 (GPIO26), U6.20 (VH)
PWMC: U1.40 (GPIO32), U6.22 (WH)
PWMR: U1.22 (GPIO22), U3.6 (IN+)
SCL1_EXT: J11.10, R25.1, U1.14 (GPIO15)
SDA1_EXT: J11.8, R26.2, U1.13 (GPIO14)
SHA: Q2.1-3 (S), Q3.5-8 (D), R9.1, R39.1
SHB: Q4.1-3 (S), Q5.5-8 (D), R10.1, R43.1
SHC: Q6.1-3 (S), Q7.5-8 (D), R11.1, R47.1
SOA: U1.49 (GPIO40_ADC0), U6.9 (CURU)
SOB: U1.52 (GPIO41_ADC1), U6.10 (CURV)
SOC: U1.53 (GPIO42_ADC2), U6.11 (CURW)
SWCLK: J3.4 (SWDCLK/TCK), U1.33 (SWCLK)
SWDIO: J3.2 (SWDIO/TMS), U1.34 (SWD)
SYNC: R50.1, U1.16 (GPIO16)
USB_CC1: C2.1, J2.A5 (CC1), U8.10 (CC1), U8.11 (CC1)
USB_CC2: C3.1, J2.B5 (CC2), U8.1 (CC2), U8.14 (CC2)
USB_PD_INT: R56.1, U1.79 (GPIO2), U8.5 (INT_N)
USB_PD_SCL: R55.1, U1.78 (GPIO1), U8.6 (SCL)
USB_PD_SDA: R54.1, U1.77 (GPIO0), U8.7 (SDA)
VBUS: C7.1, C11.1, C23.1, C24.1, C25.1, C31.1, C32.1, C33.1, D10.2 (A), D11.1 (K), J4.1, J5.1, Q2.5-8 (D), Q4.5-8 (D), Q6.5-8 (D), Q8.1-3 (S), Q9.6 (C1), R28.1, R37.2, U5.2 (EN/UVLO), U5.3 (VIN)
VBUSDIV: D4.1 (K), R28.2, R29.1, U1.54 (GPIO43_ADC3)
VDD: C8.2, C15.1, C17.1, C18.1, J11.20, L4.2, R30.1, R31.1, U3.4 (VDD), U5.8 (BD), U6.6 (12VOUT), U6.29 (VSA), U9.4 (IN)
VDDDIV: D5.1 (K), R31.2, R32.1, U1.55 (GPIO44_ADC4)
VUSB: D9.2 (A), J2.A4 (VBUS), J2.A9 (VBUS), J2.B4 (VBUS), J2.B9 (VBUS), Q8.5-8 (D), Q9.3 (C2), R57.2

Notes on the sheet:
3.3V output Fed from both USB and VBUS to allow electronics to come up form 5V USB
Additional caps on VBUS
maybe STUSB1602/PTN5110 would work for USB PD FUSB302BMPX seems smallest
4937N (30V) can do 8A continuous current on minimal pad in thermal limit NVTFS5C658NL is a similar 60V part
12V output
P-FET switch with reverse polarity protection via bipolar comparator
3V3 loads RP2354B AS5047 TMC6200 IO UART
Analog 3x Current Sense (SOx) VBUS VDD 3x Aux / Bridge Voltage
SPI0: AD5047 SPI1: TMC6200 UART1: DBG / console I2C0: FUSB302 PWM8: PWMC ENC PIO0: LED_CLK LED_MOSI PIO1: ENCA ENCB ENCI PIO2: PWMx/ENx
Gate Resistors might need higher values for low C_g MOSFETS to avoid to fast switching and induced ringing.
V0.2: VBUS feedback
SPI on STM32G4 would need an inverter on SLCK because hardware NSS only works in Motorola Mode, but DRV8323 needs reverse CPOL
clamp VBUS sense to 20V, 48V ops is not supported
on Circuithub stackup (R=4.7,h=0.2mm) use 12mil wide w/ 4mil spacing for D+/D- pair
LED has a 5V LDO supply
additional bridge voltage sensing for sensorless FOC
USB-C in USB 2.0 compat mode but with Power Delivery

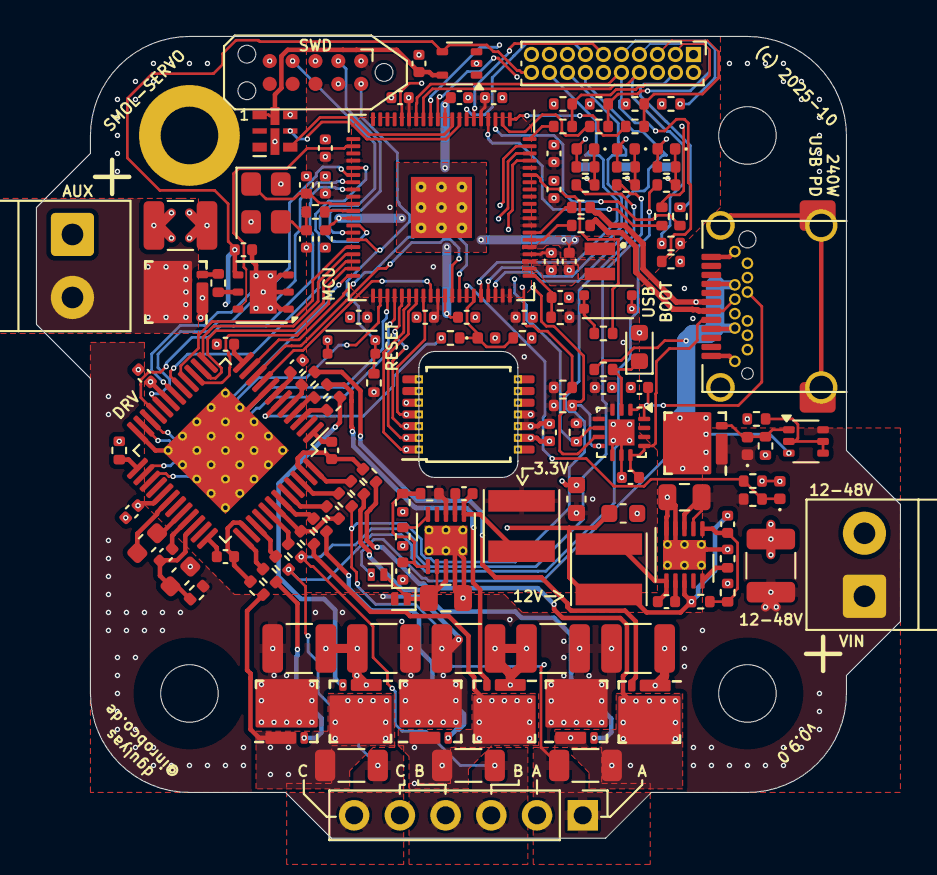
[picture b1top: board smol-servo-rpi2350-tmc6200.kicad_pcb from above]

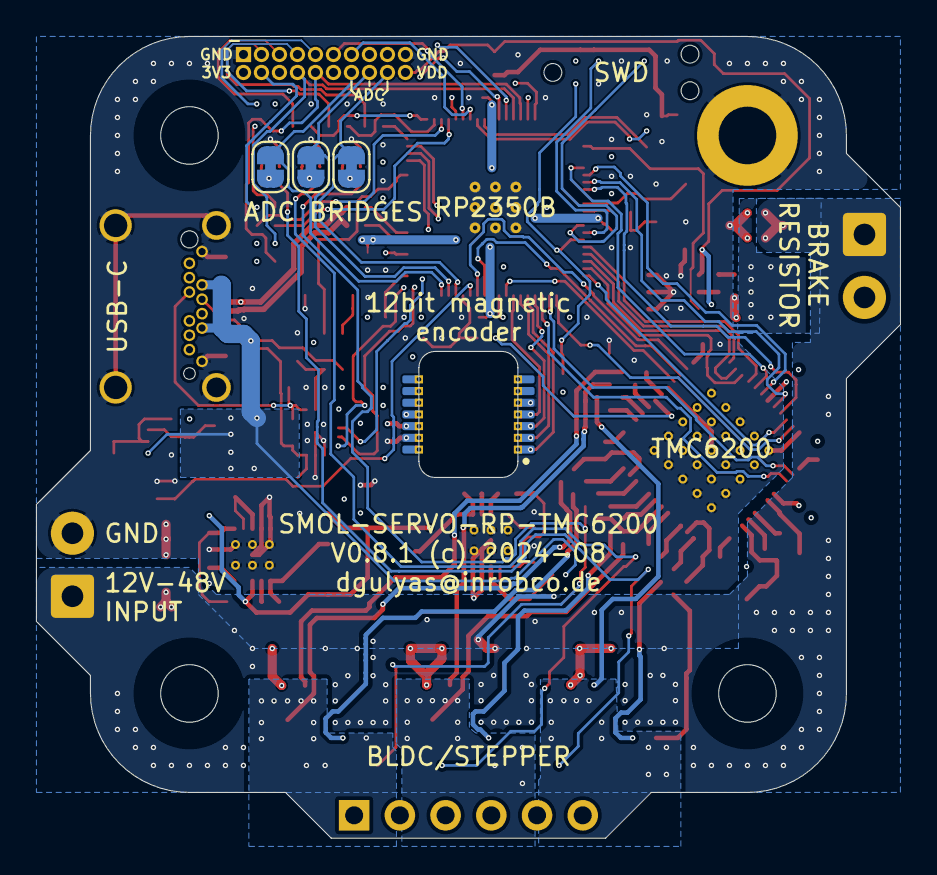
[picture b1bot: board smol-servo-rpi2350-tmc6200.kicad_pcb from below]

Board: 4 copper layers, 48.0 x 44.5 mm, 151 parts (3 on the bottom side), 123 nets.

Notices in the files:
hardware/smol-servo-rp-nodrv/smol-servo-rp-nodrv.kicad_pcb:
(c) 2026-01
V0.9.1 (c) 2025-11
hardware/smol-servo-rpi2350-tmc6200/smol-servo-rpi2350-tmc6200.kicad_pcb:
(c) 2025-10
V0.8.1 (c) 2024-08
hardware/smol-servo-tmc6200/smol-servo-tmc6200.kicad_pcb:
V0.7.0 (c) 2022-08
stm32-nema17-servo.kicad_pcb:
V0.2 (c) 2019-08
